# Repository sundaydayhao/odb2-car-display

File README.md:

# P4 汽车副屏

ESP32-P4 Function EV Board **v1.4**，原配 **7 寸 1024×600 触屏与 MIPI 摄像头**，ESP-IDF **5.5.x**、LVGL 9.2。
车辆仪表、影音中心（SD/在线 MP3、RDA5807M FM 电台、摄像头）、小智车辆查询与设备控制、闹钟、SD 诊断记录、Wi-Fi STA（路由器或手机热点）、HTTPS 上传与签名 OTA。
已移除微雪 S3 的屏幕/触摸实现，仅保留 **ELM327 BLE** 车辆数据入口，不恢复有线总线采集，也不创建 `projects`。

完整接线、C6 配套固件、配网、语音绑定、日志回放和本地服务器使用见 **[P4 上板与联调](docs/P4_BRINGUP.md)**。
尚无云服务器时，默认不上传、不自动升级；摄像头功能已启用，开机不自动采集，可通过页面或小智开启和拍照；麦克风开机后在本机识别唤醒词，唤醒后才向小智上传本轮语音。

当前固件 **0.4.0**：底部七页包含仪表、影音中心和地图轨迹。影音中心提供音乐、FM 电台、摄像头三个页签；语音助手和闹钟位于设置中。音乐支持 SD 卡根目录或 `music` 文件夹中的 MP3，也支持用户提供的 HTTP/HTTPS MP3 直链，音量统一在声音设置中调整。FM 默认 I²C0 / GPIO2 SDA、GPIO3 SCL，支持调谐、硬件搜台、收藏和全局音量；声音经模块模拟 L/R 输出，见 [FM 接收器](docs/FM.md)。地图轨迹提供离线中国概览、缩放拖动与独立串口 GPS 轨迹，未定位时显示中国地图。ATGM336H-5N 默认使用 GPIO4 / UART1 / 9600，见 [地图与接线说明](docs/MAP.md)。DHX30 温湿度空值显示在驾驶页面。摄像头默认编入，可预览、拍照保存和查看相册。

小智已注册 15 个设备 MCP 工具，可查询水温等真实车辆数据、调节音量、操作 FM 和音乐、设置闹钟及拍照。播放操作在语音回复结束后执行；缺失或过期的车辆值明确返回不可用。闹钟使用北京时间，支持单次、每天重复和倒计时；设备需保持通电。在线按歌名点歌仍需提供音乐服务/API，当前为直链播放及保存音源。详见 [小智接入与验证边界](docs/VOICE_CONTROL.md) 和 [影音中心](docs/MEDIA.md)。

2026-09-20：音乐列表移除手动刷新按钮，顶部增加播放状态及全局声音入口，音乐与语音共用保存音量；地图页去掉内层重复标题，行程与地图使用不同图标。板端补齐 B02-Z 会话握手、按能力位图分频读取、燃油流量/大气压力和连续采样的油耗/行程计算。用户车辆已确认为 2019 凯美瑞 2.5L 汽油版，具体可用范围和未接入项目见 [车辆参数映射](docs/VEHICLE_DATA_2019_CAMRY.md)。

界面视觉重设计：使用 Inkscape 制作可编辑的深浅主题稿、统一线条图标及本地音乐插画，落实到七页 LVGL 界面和设置。设计源文件与导出方式见 [CABIN 双主题设计](docs/design/cabin/README.md)。

0.3.15：顶部 SD 卡图标随识别状态更新，未检测到卡为灰色、可用为绿色、存储异常或记录已满为红色；运行中插卡会重新识别，拔卡后停止记录并更新状态。保留已有记录，不自动格式化或清空。

0.3.14：顶部状态栏与设置侧栏统一使用机身加圆形镜头的摄像头图标，支持状态颜色、深浅主题和选中态；界面预览检查通过。

0.3.13：修复打开摄像头本地预览时报“连接或格式异常”的格式请求参数。SC2336 实板已完成两次连续采集、关闭和重新打开测试，用户确认屏幕画面正常，详见 [上板记录](docs/P4_BRINGUP.md#8-验收顺序)。

0.3.12：针对联网后首次唤醒的编码等待，将本次语音编码器状态优先放入片内 RAM；已编译、烧录并确认实际分配位置，首句实测结果待补入。保留待机提前连接、约两秒真实唤醒录音和官方自动对话流程，回复后可以直接追问，空闲结束由服务端通知。

0.3.9 最终实板已验证唤醒及免唤醒直接追问，两轮回复各完整播放 105 帧，用户确认正常；随后恢复待唤醒。开机首次 DHCP 失败后自动恢复，在约 47 秒时联网；首次地址获取失败的原因仍未根治，不能把本次恢复成功视为长期无线稳定性验收。

保留 0.3.8 Wi-Fi 修复：关联、获取 IP 和失败分开显示；单轮最多三次连接、一次 DHCP 重新申请和一次无线接口恢复，耗尽预算后停止，用户重新选择网络可再次连接。

蓝牙为手动扫描、从列表选择连接；成功连接的设备自动保存，开机或意外断开只重连一次，失败后停止。0.3.6 已实测十五秒扫描结束后保持待选，没有自行连接或重复扫描；后续版本保持同一蓝牙实现。适配器暂不在现场，实际连接/保存/重连仍待验收。

0.3.7 对连接期间缓存的语音按六十毫秒一帧发送；该轮实板连续两次唤醒均收到服务端识别与语音回复，分别接收并播放 76、55 帧后回待机，用户确认听到回复，无重启。用户随后在路由器网络再次遇到获取 IP 卡住，0.3.8 继续针对网络恢复排障。

0.3.5：修复唤醒后的 MCP 初始化、客户端身份和连接时序，待绑定设备优先显示绑定码；扩充 Opus 编码任务栈以修复首次聆听时重启，后续实板编码/播放的最小剩余栈为 22,856 字节。
首次使用须在联网后说「你好小智」，到「设置 → 语音助手」查看绑定码，并在 [小智控制台](https://xiaozhi.me) 添加设备；仅连接热点尚未完成绑定。现场验证进展见 [P4 上板与联调](docs/P4_BRINGUP.md#8-验收顺序)。

2026-09-14：Android 采集 App 更新至 0.2.0，提供采集／记录／设置三页、浅深色主题和大屏分类设置，验证范围见 [App 说明](android-app/README.md)。
另有独立的 [OBDNode-C3 采集固件与硬件包](obd_interface/README.md)，源码、KiCad 原理图/PCB、器件库、3D 模型和烧录夹具均位于同一板级目录，包含停车低功耗策略。
主采集板 A1 已把 16 针直焊孔、蓝牙、CAN 和电源电路整合并完成布线，ERC／DRC／未连接项／原理图一致性均为 0；[完整 OBD 板级工程与验证记录](obd_interface/hardware/obd-ble-node/README.md)。现有插头适配、射频和停车电流仍待实物验证，不能直接用于量产；`mechanical-reference/` 只保留早期孔位对照件。

历史记录（网络播放已在 0.4.0 删除）：2026-09-11 / 固件 0.2.6 底部新增第六页「多媒体」，提供联网 MP3 音乐、网络电台、播放暂停、切换曲目/电台、停止与音量控制。
「设置 → 多媒体」保存自定义音乐/电台直链；开机不自动播放，广播通过网络收听，功能与音源说明见 [当前影音中心](docs/MEDIA.md)。
网络设置自动扫描附近 Wi-Fi，显示信号、加密方式和连接状态；点选热点后输入密码连接，开放热点无需密码，提供重新扫描与忘记网络。
设置采用平板双栏布局，左侧固定八个分类，右侧内容限制为 640 像素宽；打开齿轮默认进入显示与外观，会话内记住最后使用的分类。
「设置 → 显示与外观 → 界面主题」提供六张配色预览卡片，点选立即应用并自动保存。
浅色外观为清爽白、晴空蓝、暖沙米；保留夜行霓虹、熔岩赛道、酸性机能三种深色外观。仪表和设置页同步换色，未保存外观时默认清爽白，已有选择继续保留。
顶部状态图标和齿轮统一靠右，包含蓝牙图标，移除「搜索设备」等连接进度文字；全部设备设置集中到分类设置页。
「设置 → 蓝牙设置」点击「扫描设备」，再从名称/地址列表点选连接；可断开或忘记已保存设备。开关重启后保留，关闭后释放适配器供手机采集。
在「设置 → 网络与连接」从扫描列表选择手机热点，仅输入密码即可连接并保存；设备只运行 STA，连接失败也不开 AP。
新增 **[Android 采集 App](android-app/README.md)**，直接连接 BLE 型 ELM327，限时监听 CAN 或记录标准诊断事务，保存到手机并导出供离线分析。

## 语音唤醒与连续对话

连接 Wi-Fi 并完成校时后，说 **“你好小智”**，等小智回应后直接说问题，无需触摸或按住按钮。
回复结束后可以直接追问，不用再次唤醒；一段时间没有说话，服务端结束会话后才回到待唤醒。“设置 → 语音助手”显示唤醒词、状态和首次绑定码；绑定完成后重新唤醒。
待机音频只在本机处理，不上传；真实唤醒后上传约两秒唤醒音频及对话，断句与空闲结束由服务端控制。模型打包进应用，保持原分区及签名 OTA/回滚流程。
麦克风监听与音乐输出可同时工作；检测到唤醒后，音乐暂停。回复时不接受新的唤醒，避免设备声音再次触发。
各版本的实际唤醒、连续对话、响应时间和已知问题见 [P4 联调说明](docs/P4_BRINGUP.md#8-验收顺序)。

## 使用

1. 将支持 BLE 的 ELM327 适配器接到车辆诊断口，车辆上电。
2. 断开手机诊断软件与适配器的连接，多数适配器只允许一个客户端。
3. 首次进入「设置 → 蓝牙设置 → 扫描设备」，点选自己的适配器连接。每次扫描十五秒，扫描不会自行连接。
4. 成功初始化的适配器会被保存；下次开机、重新开启蓝牙或意外断开时只尝试重连它一次，失败后停止，等待手动选择。手动断开、关闭或忘记不会立即连回。
5. 顶部蓝牙图标显示连接状态，详情在「设置 → 蓝牙设置」查看；缺失车辆数据为 `--`。

P4 通过板载 C6 提供 Bluetooth LE，不支持 Classic SPP；标注“蓝牙 ELM327”的适配器不一定是 BLE。
参见 [官方 v1.4 板卡说明](https://docs.espressif.com/projects/esp-dev-kits/en/latest/esp32p4/esp32-p4-function-ev-board/user_guide_v1.4.html)。
适配器的蓝牙串口传输的是 ELM ASCII 指令/响应，本机不会把每个通知包误当成独立 CAN 帧。

## 已实现

- NimBLE Central 手动扫描、列表点选连接，最多显示十六个可连接设备；已保存设备只自动重连一次，失败不循环扫描或切换其他设备。
- 按完整地址和地址类型区分同名设备；自动发现服务、特征与真实 CCCD，支持 Notify/Indicate。
- FFF0、FFE0、Nordic UART 三类串口服务，以及自定义服务/特征 UUID。
- MTU 协商、写入应答/无应答、通知分片拼接、单指令串行事务、`>` 结束符和容量检查。
- 超时或溢出后关闭当前连接，隔离迟到响应；用连接代次防止旧连接数据进入新会话。
- ELM/STN 身份检查、AT 初始化、自动识别 ISO 15765-4 协议 6/7/8/9。
- 支持 PID 位图查询和单 ECU 固定；11 位/29 位响应头、填充字节、边界校验以及有界 ISO-TP 重组。
- 每项数值独立失效时间；断开连接立即清空实时有效标记，UI 不阻塞等待蓝牙。
- 可选 BLE 配对、明确配置的 SMP passkey、NVS 绑定保存。不自动覆盖冲突的旧绑定。
- 乐鑫 `esp_xiaozhi 0.1.2` + `esp-sr 2.4.6`，说“你好小智”唤醒，按官方 AUTO 流程由服务端断句并回复；回复后继续聆听，服务端结束后回待唤醒。已接入 AEC，声学效果待实板验证；不支持回复中语音打断。
- 影音中心提供 SD/在线 MP3 播放、RDA5807M FM 接收控制和摄像头预览/拍照/相册；小智支持设备查询和控制。FM 模块尚待接线实测，摄像头不录像、不上传画面，开机不自动采集。
- SD 原始事务记录与解析快照，有界容量、掉包标记和重启恢复；HTTPS 幂等上传。
- 本地 HTTPS 服务、固件签名发布、离线回放工具；P4 双 OTA 槽、手动驻车升级及启动自检回滚。

| 数据 | 标准 PID | 单位 |
| --- | --- | --- |
| 车速 | 01 0D | km/h |
| 发动机转速 | 01 0C | rpm |
| 发动机负载 | 01 04 | % |
| 节气门开度 | 01 11 | % |
| 冷却液温度 | 01 05 | °C |
| 油量 | 01 2F | % |
| 控制模块电压 | 01 42 | V |
| 进气温度 | 01 0F | °C |
| 机油温度 | 01 5C | °C |
| 进气歧管绝对压力 | 01 0B | kPa |

只轮询所选 ECU 声明支持的参数。增压相对压力不使用固定大气压猜测；档位、胎压、
变速箱温度、续航、油耗等尚未接入的参数保持不可用。副屏固件不执行清码、刷写、控制执行器或全总线监听。
手机 App 的 CAN 监听单独运行，只记录适配器在诊断口可见的经典 CAN；手机采集前需在副屏蓝牙设置中关闭车辆连接（旧固件可关闭副屏），避免争用适配器。

## 配置

在 `idf.py -B display_board/build menuconfig` 的 **ELM327 BLE Dashboard** 中配置：

- 设备选择在副屏蓝牙扫描列表完成，旧名称/地址过滤配置不再参与连接；随机地址未绑定且发生轮换时，需要重新扫描选择。
- UUID：三项同时设置或全部留空，详见 [BLE 协议实现](docs/ELM327_BLE.md)。
- 配对：默认按服务的加密要求触发；写入特征需加密的适配器可打开预先配对。
- 指令间隔：默认 50 ms；普通响应 1500 ms；初次车辆搜索 20000 ms。

工程使用显示板自己的配置：默认值由 `display_board/sdkconfig.defaults` 和 `display_board/main/Kconfig.projbuild` 提供，
当前构建配置保存在 `display_board/sdkconfig` 中，依赖缓存保存在 `display_board/managed_components/`，包含 BLE、屏幕和 PSRAM 参数。

## 构建与烧录

显示板构建产物位于 `display_board/build`，已经切换为 P4 目标。使用本机 IDF 5.5.5 环境包装器：

```powershell
.\tools\idf55.ps1 build
# 核对 v1.4 的 USB-to-UART 口，把 COMx 替换为实际串口
.\tools\idf55.ps1 -IdfArgs @('-p', 'COMx', 'flash', 'monitor')
# 配套 C6 无线固件，产物在 display_board/build/c6，通过 C6 独立编程口烧录
.\tools\build_c6.ps1
```

按官方要求使用 USB/稳压电源，不要直接接车辆 12 V。
使用 16 MB Flash、两个 6 MB 应用槽；主应用起始地址 `0x20000`。
首次在 P4 上使用完整 `flash` 写入新的引导程序、分区表、otadata 和应用，不能套用旧 S3 的地址或只执行 `app-flash`。
NVS 不会在失败时自动擦除；没有卡时记录状态为不可用，SD 卡不会被自动格式化。

## 代码结构

两块实体板已经按板级职责各自保存完整工程：

| 目录 | 板卡与职责 |
| --- | --- |
| `display_board/` | ESP32-P4 显示板板级包：`main/` 固件源码、`hardware/` 原理图/PCB/器件库/3D 外壳、`managed_components/` 和 `sdkconfig` |
| `obd_interface/` | ESP32-C3 OBD 接口板板级包：`main/` 固件源码、`hardware/` 原理图/PCB/器件库/3D/夹具、独立 `sdkconfig.defaults` |

显示板使用 `display_board/CMakeLists.txt`、`display_board/sdkconfig`、`display_board/managed_components` 和 `display_board/build` 作为独立 ESP-IDF 工程；仓库根目录不再保存某块板的源码或工程配置，只保留跨项目工具、文档和共享测试输出。OBD 接口板是可独立配置、构建和烧录的 ESP-IDF 工程。

| 文件 | 职责 |
| --- | --- |
| `display_board/main/elm327_ble.c` | NimBLE 连接、服务订阅、串行传输和重连 |
| `display_board/main/elm327_protocol.c` | 有界 ASCII/ISO-TP 响应解析，不依赖硬件 |
| `display_board/main/obd2.c` | AT 会话、能力发现、参数调度与快照发布 |
| `display_board/main/obd2_decode.c` | 数值换算和逐字段过期策略，不依赖硬件 |
| `display_board/main/ui.c` | 官方 BSP 屏幕/触摸、线程锁及显示模型映射 |
| `display_board/main/dashboard.c` | 七页彩色界面、主题、手动导航、显式演示模式 |
| `display_board/main/service_panel.c` | 唯一齿轮入口、分类设置、屏幕配网、外观、语音/摄像头/上传/更新交互 |
| `display_board/main/voice_service.c`、`display_board/main/camera_service.c` | 小智音频链路与本地摄像头预览 |
| `display_board/main/recorder.c`、`display_board/main/cloud_service.c` | SD 记录、HTTPS 上传、签名 OTA |
| `display_board/main/device_services.c`、`display_board/main/network_service.c`、`display_board/main/device_console.c` | NVS 设置、热点 STA 与串口配置 |
| `tools/lab_server.py`、`tools/replay_recording.py` | 本地诊断服务、升级发布与原始记录回放 |
| `android-app/` | Android BLE 连接、ELM 会话、前台限时采集、本地记录与导出 |
| `tools/analyze_android_capture.py` | 手机 JSONL 完整性检查、CAN 帧/通信事件 CSV 与汇总 |

## 验证

2026-09-15 / 0.3.0：唤醒词版本在 ESP-IDF 5.5.5 下构建通过，应用 5,731,648 字节，现有 6 MiB OTA 槽剩余 559,808 字节。
5 项 C 测试、18 项 Python 测试及 8267 个同源界面标签检查通过，语音设置页已人工查看。
固件内 WakeNet/VAD 共 579,144 字节，与固定版本组件模型逐文件核对一致；随后完整烧录到 COM28，四个镜像校验通过。
65 秒启动观察确认版本、Wi-Fi 连接及校时、BLE 扫描和唤醒待机状态，串口已释放；实板声学表现仍待验证，日志见 `build/flash-0.3.0-20260915/`。

新实现与实板待验收边界见 [P4 上板与联调](docs/P4_BRINGUP.md)。原有
[产品与系统总体规划](docs/PRODUCT_ARCHITECTURE.md) 保留为历史讨论，不能作为当前平台选择或功能已验证的依据。

本机运行 `.\tools\run_host_tests.ps1`，测试产物均在 `build` 内。
2026-09-14 提交前复核：P4 0.2.6 在 IDF 5.5.5 下构建通过；4 项 C 测试、18 项 Python 测试和 8265 个同源界面标签／交互检查通过。本轮未新增实板烧录或实车验证。

2026-09-11 / 0.2.2：P4 构建和 3907 个同源界面标签/交互检查通过，已在 COM28 完整烧录并校验。
14 项实板蓝牙检查通过：关闭后停止扫描、关闭/开启状态重启保存、禁用时拒绝重连、开启及手动重连恢复扫描；最终恢复蓝牙开启，串口已释放。
本次未连接真实适配器，设备断连和正在传输时切换仍待实机覆盖。日志在 `build/flash-0.2.2-20260911/`。

2026-09-11：P4 0.2.1 构建通过，应用约 2.50 MiB，6 MiB OTA 槽剩余 58%；2 项 C 测试、18 项 Python 测试通过，
同源 UI 检查 3570 个标签无错误。Android 0.1.0 Debug APK 构建、17 项协议测试和 Lint 检查通过。
随后按用户要求在 COM28 完整烧录 P4 0.2.1，四个镜像写入校验通过；观察 65 秒无崩溃或再次重启，屏幕/触摸初始化、STA 启动和 BLE 扫描正常。
仍有 C6 版本不匹配、SD 卡不可用提示，热点尚未配置。未烧录 C6 或连接 Android 手机；热点连接、实体触摸/亮度、真实 ELM 采集与手机后台运行仍待验收。
本次烧录与启动日志位于 `build/flash-0.2.1-20260911/`。

2026-09-08：IDF 5.5.5 下 P4 主固件和配套 C6 固件均构建通过；2 项 C 协议/升级策略测试、
10 项 HTTPS/签名/回放测试通过，同源 UI 检查 4808 个标签无错误，并人工检查截图。
启用公钥的 OTA 分支另行构建通过，默认配置已恢复为未配置服务器/信任目录、禁止台架升级绕过。
随后已在 COM28 完整烧录 P4，并修正 Hosted 传输池片内内存不足、Wi-Fi/BLE 并发初始化共享总线导致的重启。
修正后观察 65 秒无崩溃/重启，屏幕和 GT911 初始化成功、BLE 持续扫描、串口状态正常；物理触摸操作仍待人工验收。
板载 C6 报告版本不匹配，本轮未烧录 C6；存储卡初始化失败、热点未配置。
尚未验证实板音视频、真实车辆连接、设备端上传和 OTA 掉电回滚。
测试包含每个通知分片边界、回显、提示语、多个 ECU、两类响应头、ISO-TP 序号错误、截断、溢出、
负响应、不支持参数、换算、逐字段过期和随机字节输入。板端 UI 同源测试见 [UI 说明](docs/UI_DESIGN.md)。

实际适配器的 UUID、配对方式和响应行为需要实机确认，软件测试不等同于已经连通真实车辆。
**历史 S3 验证（不适用于当前 P4 固件）**：2026-09-06 曾构建并烧录到 COM9，写入校验成功；启动后观察 65 秒，
屏幕/触摸初始化及 BLE 扫描正常，未发现崩溃。观察期间未连接到匹配的适配器，尚未完成真车数据验收。

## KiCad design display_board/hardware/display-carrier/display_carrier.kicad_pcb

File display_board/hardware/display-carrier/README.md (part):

# OSPTEK P4C5 / P4C6 显示底板

2026-09-25，修订 R：五类器件、八个位置按价格/交期调整，原理图、PCB 与单板 BOM 同步。导出不含批量、备料或起订量放大；误配商品与 DNP 单独列出。见 [当前采购说明](PROCUREMENT.md) 和 [成本、交期与兼容性](COST_REDUCTION.md)。

**当前主工程：修订 R（单板 BOM 与价格/交期调整）。** 保留触摸/LCD 穿孔，调整主控和摄像头接口；打开本目录 `display_carrier.kicad_pro`。`../display-carrier-revision-L/` 保留历史 L1 副本。

2026-09-25，转角修正：消除四处 MIPI 等长补偿锐角，改用展开的 45° 补偿段；增加实际铜线转角检查，物理 DRC、差分匹配与参考地复核通过。见 [布线复核](ROUTING.md)。

2026-09-25，修订 Q：99 个电阻和 56 个电容改为 0402，原理图/PCB/采购表同步。采用嘉立创 JLC04161H-3313、名义 1.6 mm；DSI/CSI 六组差分已布线并补内层参考地、换层回流过孔和时钟分段屏蔽。工程仍为部分布线，电源/USB/射频/音频及原有电路缺口尚待继续。见 [0402 清单](PASSIVE_SHRINK.md) 与 [布线依据和检查范围](ROUTING.md)。

2026-09-24，修订 P：按立创大陆站库存完成全板定料/替换；ES8388、FSV4730、SHT40 膜版及开关、电感、电容等已同步 SCH/PCB。85 个具体料号覆盖 328 个装配位置（84 个直营、1 个合作供应）；仅 F300 需电池条件定型，主控/ML307 保留。新 FM 不支持 RDS，Codec/FM 需驱动迁移。见 [替换与库存核查](SOURCING_REVIEW.md) 和 [当前单板采购表](PROCUREMENT_PER_BOARD.csv)。

2026-09-24，修订 N：主控上移 6 mm，LCD 焊盘间距增至 8.88 mm；摄像头座移至右下方。12 根 MIPI 信号在独立临时板几何试连通，主工程仍未布线。见 [本轮布局与试布边界](MIPI_LAYOUT.md)。

2026-09-24，修订 L1：J300 改为 J301 同款 **JST B2B-PH-K-S(LF)(SN) / C131337**，PH 2.0 mm、立式 2Pin。原理图、PCB、3D 和采购表同步，电池 1 脚为正极、2 脚接地。PH 额定 2 A（AWG24），原高功率电池预算不再适用，F300 改为待选型；详见 [端子变更与电流限制](J300_TERMINAL.md)。

2026-09-23，修订 L：按 **100 块＋20% 备料**建立立创优先采购表。每板 300 个装配位置当前归入 72 个具体立创料号（L1 合并 J300 后），鱼鹰核心板/ML307 两项单采，18 个位置仍需闭合；库存为当日未锁定快照。麦克风、模拟开关、FM 稳压器和功放分压已同步 SCH/PCB/封装。见 [采购与替代依据](PROCUREMENT.md)、[现行单板表](PROCUREMENT_PER_BOARD.csv)、[逐位号表](PROCUREMENT_REFERENCES.csv)。

2026-09-23，修订 K：**F 面朝后壳，B 面朝屏幕**。FPC 座、高 2Pin 接口及全部器件本体集中到 F 面，增加触摸 10×3 mm、LCD 20×3 mm 两处实际穿线槽。B 面无器件本体，但通孔脚仍名义露出最高约 2.4 mm，需绝缘间隙；槽位与穿板线长待实物确认。见 [正反面装配说明](SCREEN_BACK_ASSEMBLY.md)。

修订 J 保留：L400 改为国产长江微电 **FEXU0640S2R2MGS / C54140025**，2.2 µH，6.2×6.0×4.0 mm；SCH/PCB/3D 已同步。见 [电感选型与核算](INDUCTOR_SELECTION.md)。

修订 I 保留：SIM 改为 **GCT SIM8066 按压自锁 Nano-SIM**，从屏幕正视的右侧推入、再次按压弹出。原理图/PCB/3D 已同步；卡检测及上拉按 ML307A 手册修正。见 [SIM 卡座与外壳要求](SIM_SOCKET.md)。

修订 H 保留：新增板载 **RDA5807M**，音频改为 **ES8389 + 两颗直接焊载板的 MEMS 麦克风 + 两只 NS4150B / 两路扬声器接口**，参考 ESP32-S31-Korvo-1 官方结构；主控仍为 P4C5/P4C6。见 [音频架构与固件迁移](AUDIO_ARCHITECTURE.md)。

修订 G 的原始测量继续保留：总成顶部到原平面折后尖端 **触摸 7.5 mm / LCD 46.1 mm**。板框 145×85 mm，PCB 顶部偏移 2.50 mm。修订 K 将坐标改为屏幕背视，插座暂加 4 mm 穿板长度补偿，不能当作已确认的插接位置；光照/温湿度及隔热槽保留。见 [当前布局](FPC_FIT_REVIEW.md)、[传感器](CABIN_SENSORS.md)。

当前 20 页原理图、361 个电路封装＋4 安装孔，338 个实体器件均有可加载模型，默认装配 331 个；7 个互斥配置/射频调谐件保持 DNP。**部分布线，519 项未连接，整机电路尚有既有缺口，不能投板。** ERC 0 error / 13 个既有 warning；原生物理 DRC、SCH/PCB 一致性 0 违规。检查边界见 [设计状态](DESIGN_STATUS.md)。

按本轮要求放弃原裸 P4＋C6 单板方案，重新设计一块集成外围功能的底板。一个 25 × 25 mm、88 针邮票孔位置，择一贴装 OSPTEK ESP32-P4C5-Core 或 ESP32-P4C6-Core。兼容指同一 PCB 的两种装配配置，不是两个核心板同时装，也不是可热插拔的插座。

旧 `../display-singleboard/` 仅作历史记录，不作为新板的布局、电源或布线起点。本轮新增 [KiCad 工程](display_carrier.kicad_pro)、[原理图](display_carrier.kicad_sch)、[PCB 初摆](display_carrier.kicad_pcb)、[电气核算](ELECTRICAL_REVIEW.md) 和 [装配配置](ASSEMBLY_VARIANTS.csv)。已有资料包括[88 针核对表](CORE_PIN_COMPATIBILITY.csv)、[GPIO 分配](GPIO_PLAN.csv)、[可选 4G/GNSS 设计](OPTIONAL_LTE_GNSS.md)、[ML307A-GCLN 接线规划](MODEM_PIN_PLAN.csv)、[布局示意](FLOORPLAN.svg) 和 [资料版本记录](SOURCE_AUDIT.json)。

修订 C 的主要决定：蜂窝模组改为 17.7 × 15.8 mm、94 脚 LGA 的 ML307A-GCLN；采用内部 USB RNDIS 网卡作为联网首选、UART0 独立控制；3.8 V 降压和至少 2 × 220 µF 储能靠近模组布置。GPIO24/25 改为 USB 检测电源和 GNSS 有源天线电源控制，不再保留这两脚的 USB-FS 维修用途。外部 CH343P USB-C 充电/串口下载、屏幕/触摸、摄像头、SD、音频/FM 和双核心板兼容规划继续保留。

## 1. 核心板兼容性

已对照本机两款核心板的 88 针表、内部连接图、尺寸图，以及底板使用指南 2026.09.10 中的 V1.5 原理图。

| 项目 | 核对结果 / 设计决定 |
| --- | --- |
| 封装 | 两份图均为 25 × 25 mm、每边 22 针、1.0 mm 节距；C6 图片外形公差标 ±0.3 mm，按较大公差留装配余量。已导入两份 PcbLib 核对 88 脚名义坐标；共用焊盘按 C5 非 EP 版调整，详见 FOOTPRINT_SOURCES.md。公差、钢网和实际焊接仍待验证 |
| 电源 | 核心板 85/86 脚输入 3.3 V；84 脚 RTC_VBAT 接受控 3.3 V，不能悬空或直接接满电 4.2 V 电池；66 脚是 LDO 输出，不能当电源输入 |
| 共用外围 | P4 GPIO、DSI、CSI、USB 专用信号在两款 88 针表中对应一致；全部产品外设只接 P4 |
| 差异脚 | 6～11 脚分别为 C5 GPIO28/27/26/25/24/23 与 C6 GPIO15/14/13/9/8/7，不接通用外设 |
| 无线下载 | 共用 UART：4=RF_RX、5=RF_TX；RF_BOOT 用互斥 0 Ω 电阻选择 C5 的 6 脚或 C6 的 9 脚。C5 下载还需 7 脚 GPIO27 高；C6 下载需 10 脚 GPIO8 高，先核对模组已有上拉再决定底板配置 |
| 内部占用 | P4 GPIO14～19 为内部无线 SDIO，GPIO6 接无线 GPIO2，GPIO54 控制无线 EN；都不能再分给底板功能 |
| P4 启动 | 外加 CHIP_PU 复位 RC；GPIO35 接 BOOT，GPIO36 保持下载要求的高电平。GPIO34～38 不挂会影响启动采样的负载 |
| 无线天线 | 复用核心板 IPEX-1，采用厂商双频 FPC 天线，布置于后壳塑料区、避开屏幕金属背板和电池；C6 仅用其 2.4 GHz 频段。核心板 RF 焊盘不再接一条并联天线支路 |
| 软件 | 仓库 C5 产品描述为 P4 v3.x、C6 为 v1.3；采购批次需读芯片版本。P4 v1.x/v3.x 必须分别编译固件，C5/C6 的 ESP-Hosted 从机固件也分别管理。IDF 5.5 系列至少采用支持实际芯片的补丁版，v3.x 最低 5.5.3；若使用 v3.2 外部 32 kHz 晶体则按官方告知要求 5.5.5+ |

P4C6 可作成本配置，P4C5 可作双频 Wi-Fi 配置；不按目录名称推定今后批次的 P4 硅版本。

无线维修下载时需要使 P4 保持复位、GPIO54 不驱动无线 EN，再由夹具控制 RF_EN/BOOT/UART，防止并联输出争用。底板只留内部维修点；日常 P4 下载使用外部 USB-C。

OBD 通信按自研 BLE 节点规划。C5/C6 的蓝牙能力是 Bluetooth LE，不能把经典蓝牙 SPP 型 ELM327 视作可直接连接的设备；若仍要兼容该类 ELM327，需要额外的经典蓝牙桥接硬件。本版先不增加桥接器，避免扩大成本和无线调试范围。[C5 官方能力](https://www.espressif.com/en/products/socs/esp32-c5)、[C6 官方能力](https://www.espressif.com/en/products/socs/esp32-c6)。

## 2. 功能和器件选择

以下是候选器件和接口方向，尚不是已核价或已锁库存的量产 BOM。优先沿用供应商公开且可购买的型号；不要以淘宝存在同名商品代替正品、版本和持续供货确认。

| 功能 | 首版规划 | 选型与限制 |
| --- | --- | --- |
| 核心 | OSPTEK P4C5-Core / P4C6-Core | 同一封装、两套配置电阻/BOM；官方淘宝店为鱼鹰光电工厂店 |
| LCD | LCM-070WS209-A0，7 寸 1024 × 600，JD9165BA | 专用 30P、0.5 mm FPC；按用户 PDF 针序重新绘制，不能复制 OSPTEK YDP400BT001-V4 的 30P 屏口 |
| 触摸 | 独立可选的 I2C 触摸接口 | 与 LCD 座同在朝屏面，横向放置、入口同朝下；按照片镜像估算 PCB X=36 mm，横向仍待实测。预留 3.3 V、GND、SDA、SCL、INT、RST；脚序和接触面待定。当前接口器件均装配；无触摸款不接触摸排线，固件正常进入显示模式 |
| 可选 4G＋定位 | 中移 **ML307A-GCLN**，型号已由用户选定 | 17.7 × 15.8 × 2.4 mm、LGA94；同板选装 GPS/北斗、Nano-SIM、LTE/GNSS 双天线、电源及电平转换。标准 AT 固件＋内部 USB RNDIS 优先；具体固件/描述符/GNSS 并发仍需样品验证，不能用 ML307R 或 A-D 系列代替 |
| 摄像头 | OSPTEK ESP32-P4-Camera / SC2336，2 MP | 一个 24P、0.5 mm CSI 接口；按其原生 24P 定义，预留 2.8/1.8 V、电平转换及 24 MHz 时钟；公开 24P 针序没有外接 1.5 V 脚，不向 NC 引脚供电，DVDD 来源待厂家确认。J1220 和 CSI 针序已绘制；摄像头电源、时钟和电平转换仍待完成 |
| 音频 Codec | ES8388，已绘制 | 双 ADC / 双 DAC；7 位 I²C 0x10；标准 I²S，需迁移驱动 |
| 板载双麦克风 | LinkMems **LMA3729T381-OAS02 ×2** | 直接焊在 F 面，131 mm 中心距；顶声孔朝后壳，取消外接咪头小板 |
| 双扬声器 | 两个独立 4 Ω 扬声器，额定 ≥3 W 为候选要求 | 分别接 J820/J821 PH 2P，BTL 两端均不能接地；声腔/外形和采购型号待确认 |
| 双功放 | **NS4150B ×2**，已绘制 | 独立 4.68 V 降压供电，共用 AMP_EN；目标及音量限制按 THD/温升实测，不沿用旧 5 W 输出目标 |
| FM | **板载 FSV4730-D60-GU**，已绘制；无 RDS | 3.0 V 可关断电源、32.768 kHz 晶体、I²C 隔离和 J810 天线口；左右声道独立；射频与起振待验证 |
| 音源切换 | SN74LVC1G3157 ×4 | 分别切换左右声道正负两条模拟线；默认 DAC，切 FM 前先静音两只功放 |
| USB-UART | **CH343P**＋自动下载电路 | 唯一外部 USB-C 同时充电、日志、P4 烧录；D+/D−只进入 UART 桥。无线芯片另外留内部维修烧录触点，避免为日常用户增加选择拨码 |
| Nano-SIM | **GCT SIM8066-6-1-14-01-A** | 按压自锁、右侧插入、带常闭检测；当前厂家 Rev B 与实物壳体配合待核对，见 SIM_SOCKET.md |
| microSD | 带检测脚的自弹 TF 卡座，4 bit SDMMC | R0 已画 3.3 V 可关断供电和串阻；卡座 ESD 与断电 IO 防反灌尚未闭合。首版按 3.3 V 模式验证，不默认支持 1.8 V UHS |
| 电池充电 | **BQ25896**，替换原 SGM41513 候选 | NVDC、NTC、PSEL，不占用 USB 数据线；厂商给出最高 9 A 电池放电通路，按整机热设计降额。充电仍设 1～1.5 A；这里不是 9 A 充电。与旧候选不是焊盘直接替换 |
| USB 电流识别 | **TUSB320LAI**，固定 Sink | R0 用 GPIO 模式，仅使用“至少 1.5 A”信号，3 A 也保守按 1.5 A 档处理。TPS2553 限流最坏上限约 439 / 1253 mA；另计 USB 桥消耗。详见 ELECTRICAL_REVIEW.md |
| 主电源 | **TPS61088**→5 V；**TLV62569**→3.3 V | 5 V 主路改按 4 A 峰值目标及封闭壳热预算设计，3.3 V 主路目标 2 A；整机同时负载受功率预算约束。开关电流额定值不等于可持续输出电流 |
| 可选 4G 电源 | **TLV62585**：5 V→3.8 V，3 A 支路候选 | 放在右侧模组附近，按 GCLN 较新兼容手册的 **3.4～4.3 V** 约束，2 A 发射瞬态；至少 2 × 220 µF 近端储能，独立关断/主动放电/电流测点。USB 检测 5 V 和 GNSS 天线偏置单独可控，不直连 SYS |
| LCD 偏置 | **TPS65150** 候选，另加 1.8 V LDO | 可调 AVDD/VGH/VGL 和 VCOM 缓冲、可设置启动延时；需针对屏幕实际电流和断电放电顺序验算后选定，不沿用旧板齐纳钳位做法 |
| 背光 | **SY7200** 恒流升压候选 | 3 串 9 并，180 mA 总电流，LED 8.1～9.9 V；PWM 调光、开路保护、关机断电；电感/采样电阻额定值按计算选择 |
| 车内光照 / 温湿度 | OPT3001DNPR + SHT40-AD1B-R2，已绘制并放置 | 系统 I²C 0x45 / 0x44；光窗、独立通风与校准待验证，不替代板温/电池 NTC |
| 电量与温度 | 电量计接口/候选 CW2015＋板温 NTC | 电量计需对应电池模型，型号及供货再锁；板温与电池温度分别测量，不能用单个电压值宣称准确电量 |
| 按键 | RST、BOOT 侧按；电源侧滑 | 通过壳体侧孔/导向柱可操作；电源外部拨帽建议 10～14 mm，行程按实物开关定义，开关只承载控制电流 |

已将 99 个电阻、56 个电容改为 **0402（公制 1005）**，逐位号见 PASSIVE_SHRINK.md。大容量 MLCC 按直流偏压后的有效电容选 0805/1206；背光、电源电感按饱和电流选屏蔽功率封装，不用 0603 信号电感替代。功率与有效容量受限的位置保留较大封装。

## 3. 屏幕适配必须先闭合的事项

LCM PDF 给出 VDD/VDDIO 1.8 V、AVDD 9.8 V、VGH 18～20 V、VGL −8.5～−7.5 V、VCOM 典型 3.3 V。RESET、STBYB、方向脚均在 1.8 V 域，不能直拉 3.3 V。VCOM 用缓冲驱动并留校准值，不把无源分压视作已经验证的面板驱动。

STBYB、RESET、逻辑电源、偏置使能、背光各有独立控制及安全默认状态。按 PDF 第 8～9 页实施启动/关机，包括偏置电源之间的延时和掉电约 100 ms 的保持窗口；硬件电源开关转为关机请求，保留受控关机时间，不能直接在面板工作时切掉所有电源。

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
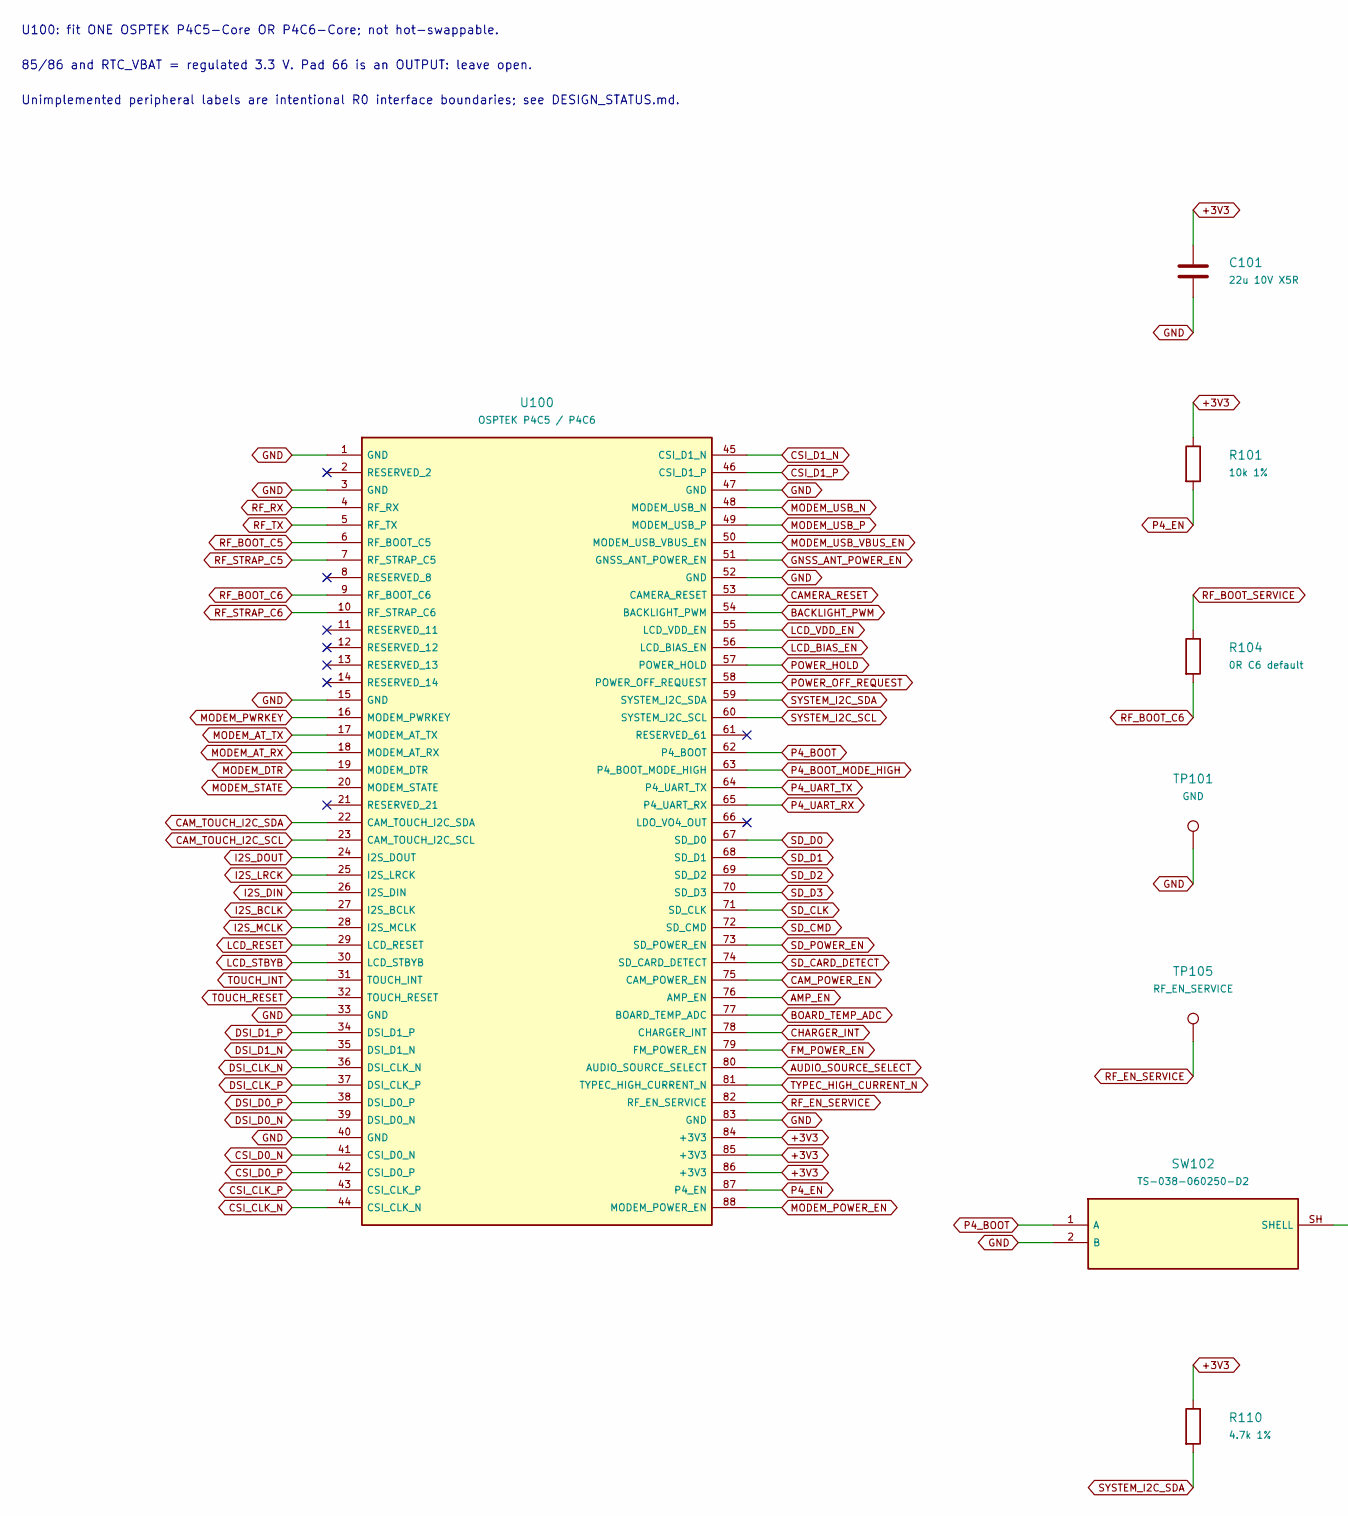
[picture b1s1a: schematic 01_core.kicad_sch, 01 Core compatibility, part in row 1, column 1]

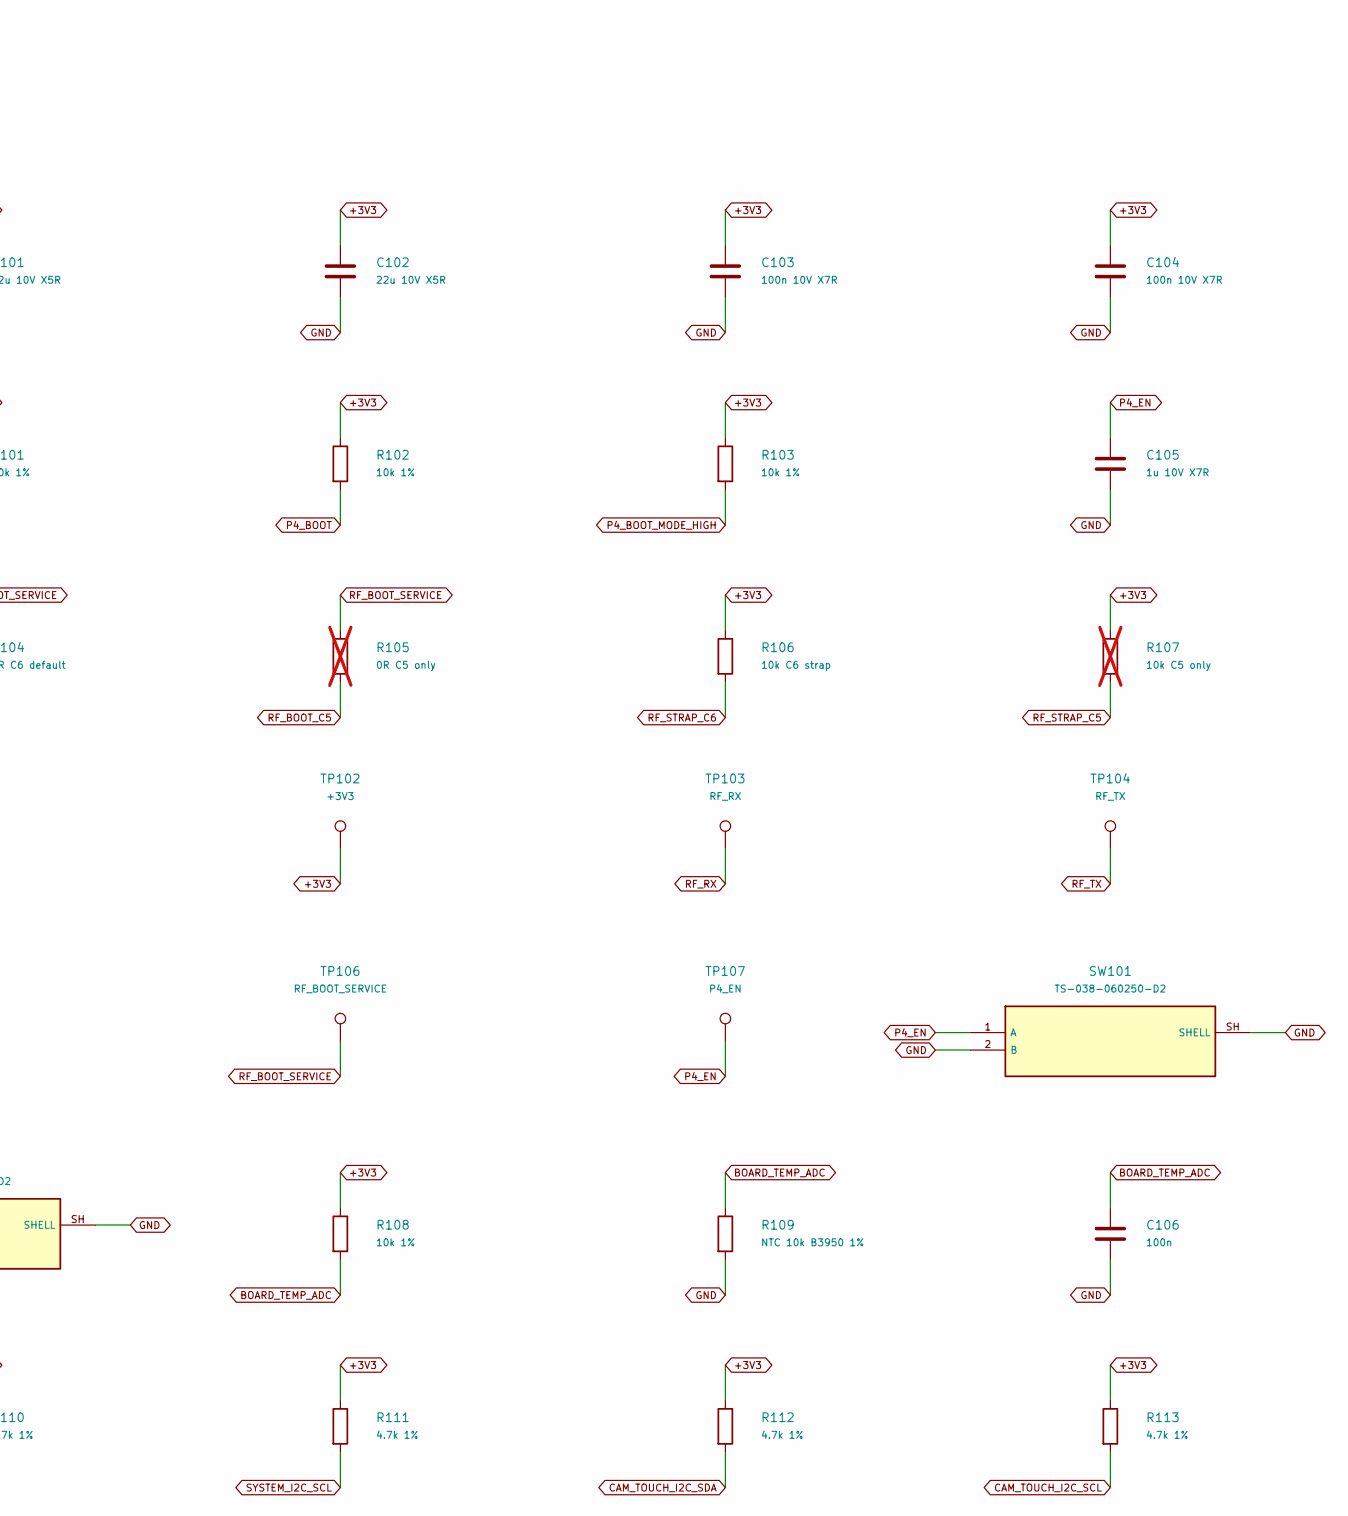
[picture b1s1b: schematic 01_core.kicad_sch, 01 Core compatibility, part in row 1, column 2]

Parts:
C101, C102: 22u 10V X5R; C_0805_2012Metric
C103, C104: 100n 10V X7R; C_0402_1005Metric
C105: 1u 10V X7R; C_0603_1608Metric
C106: 100n; C_0402_1005Metric
R101, R102, R103, R108: 10k 1%; R_0402_1005Metric
R104: 0R C6 default; R_0603_1608Metric
R105: 0R C5 only; R_0603_1608Metric; not fitted
R106: 10k C6 strap; R_0402_1005Metric
R107: 10k C5 only; R_0402_1005Metric; not fitted
R109: NTC 10k B3950 1%; R_0603_1608Metric
R110, R111, R112, R113: 4.7k 1%; R_0402_1005Metric
SW101, SW102: TS-038-060250-D2; TS038_SideKey
TP101: GND; TestPoint_Pad_D1.5mm
TP102: +3V3; TestPoint_Pad_D1.5mm
TP103: RF_RX; TestPoint_Pad_D1.5mm
TP104: RF_TX; TestPoint_Pad_D1.5mm
TP105: RF_EN_SERVICE; TestPoint_Pad_D1.5mm
TP106: RF_BOOT_SERVICE; TestPoint_Pad_D1.5mm
TP107: P4_EN; TestPoint_Pad_D1.5mm
U100: OSPTEK P4C5 / P4C6; OSPTEK_P4C5_P4C6_Compatible

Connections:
+3V3: C101.1, C102.1, C103.1, C104.1, R101.1, R102.1, R103.1, R106.1, R107.1, R108.1, R110.1, R111.1, R112.1, R113.1, TP102.1, U100.84 (+3V3), U100.85 (+3V3), U100.86 (+3V3); also elsewhere on the board
AMP_EN: U100.76 (AMP_EN); also elsewhere on the board
AUDIO_SOURCE_SELECT: U100.80 (AUDIO_SOURCE_SELECT); also elsewhere on the board
BACKLIGHT_PWM: U100.54 (BACKLIGHT_PWM)
BOARD_TEMP_ADC: C106.1, R108.2, R109.1, U100.77 (BOARD_TEMP_ADC)
CAMERA_RESET: U100.53 (CAMERA_RESET)
CAM_POWER_EN: U100.75 (CAM_POWER_EN)
CAM_TOUCH_I2C_SCL: R113.2, U100.23 (CAM_TOUCH_I2C_SCL); also elsewhere on the board
CAM_TOUCH_I2C_SDA: R112.2, U100.22 (CAM_TOUCH_I2C_SDA); also elsewhere on the board
CHARGER_INT: U100.78 (CHARGER_INT); also elsewhere on the board
CSI_CLK_N: U100.44 (CSI_CLK_N); also elsewhere on the board
CSI_CLK_P: U100.43 (CSI_CLK_P); also elsewhere on the board
CSI_D0_N: U100.41 (CSI_D0_N); also elsewhere on the board
CSI_D0_P: U100.42 (CSI_D0_P); also elsewhere on the board
CSI_D1_N: U100.45 (CSI_D1_N); also elsewhere on the board
CSI_D1_P: U100.46 (CSI_D1_P); also elsewhere on the board
DSI_CLK_N: U100.36 (DSI_CLK_N); also elsewhere on the board
DSI_CLK_P: U100.37 (DSI_CLK_P); also elsewhere on the board
DSI_D0_N: U100.39 (DSI_D0_N); also elsewhere on the board
DSI_D0_P: U100.38 (DSI_D0_P); also elsewhere on the board
DSI_D1_N: U100.35 (DSI_D1_N); also elsewhere on the board
DSI_D1_P: U100.34 (DSI_D1_P); also elsewhere on the board
FM_POWER_EN: U100.79 (FM_POWER_EN); also elsewhere on the board
GND: C101.2, C102.2, C103.2, C104.2, C105.2, C106.2, R109.2, SW101.2 (B), SW101.SH (SHELL), SW102.2 (B), SW102.SH (SHELL), TP101.1, U100.1 (GND), U100.3 (GND), U100.15 (GND), U100.33 (GND), U100.40 (GND), U100.47 (GND), U100.52 (GND), U100.83 (GND); also elsewhere on the board
GNSS_ANT_POWER_EN: U100.51 (GNSS_ANT_POWER_EN); also elsewhere on the board
I2S_BCLK: U100.27 (I2S_BCLK); also elsewhere on the board
I2S_DIN: U100.26 (I2S_DIN); also elsewhere on the board
I2S_DOUT: U100.24 (I2S_DOUT); also elsewhere on the board
I2S_LRCK: U100.25 (I2S_LRCK); also elsewhere on the board
I2S_MCLK: U100.28 (I2S_MCLK); also elsewhere on the board
LCD_BIAS_EN: U100.56 (LCD_BIAS_EN)
LCD_RESET: U100.29 (LCD_RESET); also elsewhere on the board
LCD_STBYB: U100.30 (LCD_STBYB); also elsewhere on the board
LCD_VDD_EN: U100.55 (LCD_VDD_EN); also elsewhere on the board
MODEM_AT_RX: U100.18 (MODEM_AT_RX); also elsewhere on the board
MODEM_AT_TX: U100.17 (MODEM_AT_TX); also elsewhere on the board
MODEM_DTR: U100.19 (MODEM_DTR); also elsewhere on the board
MODEM_POWER_EN: U100.88 (MODEM_POWER_EN); also elsewhere on the board
MODEM_PWRKEY: U100.16 (MODEM_PWRKEY); also elsewhere on the board
MODEM_STATE: U100.20 (MODEM_STATE); also elsewhere on the board
MODEM_USB_N: U100.48 (MODEM_USB_N); also elsewhere on the board
MODEM_USB_P: U100.49 (MODEM_USB_P); also elsewhere on the board
MODEM_USB_VBUS_EN: U100.50 (MODEM_USB_VBUS_EN); also elsewhere on the board
P4_BOOT: R102.2, SW102.1 (A), U100.62 (P4_BOOT); also elsewhere on the board
P4_BOOT_MODE_HIGH: R103.2, U100.63 (P4_BOOT_MODE_HIGH)
P4_EN: C105.1, R101.2, SW101.1 (A), TP107.1, U100.87 (P4_EN); also elsewhere on the board
P4_UART_RX: U100.65 (P4_UART_RX); also elsewhere on the board
P4_UART_TX: U100.64 (P4_UART_TX); also elsewhere on the board
POWER_HOLD: U100.57 (POWER_HOLD); also elsewhere on the board
POWER_OFF_REQUEST: U100.58 (POWER_OFF_REQUEST); also elsewhere on the board
RF_BOOT_C5: R105.2, U100.6 (RF_BOOT_C5)
RF_BOOT_C6: R104.2, U100.9 (RF_BOOT_C6)
RF_BOOT_SERVICE: R104.1, R105.1, TP106.1
RF_EN_SERVICE: TP105.1, U100.82 (RF_EN_SERVICE)
RF_RX: TP103.1, U100.4 (RF_RX)
RF_STRAP_C5: R107.2, U100.7 (RF_STRAP_C5)
RF_STRAP_C6: R106.2, U100.10 (RF_STRAP_C6)
RF_TX: TP104.1, U100.5 (RF_TX)
SD_CARD_DETECT: U100.74 (SD_CARD_DETECT); also elsewhere on the board
SD_CLK: U100.71 (SD_CLK); also elsewhere on the board
SD_CMD: U100.72 (SD_CMD); also elsewhere on the board
SD_D0: U100.67 (SD_D0); also elsewhere on the board
SD_D1: U100.68 (SD_D1); also elsewhere on the board
SD_D2: U100.69 (SD_D2); also elsewhere on the board
SD_D3: U100.70 (SD_D3); also elsewhere on the board
SD_POWER_EN: U100.73 (SD_POWER_EN); also elsewhere on the board
SYSTEM_I2C_SCL: R111.2, U100.60 (SYSTEM_I2C_SCL); also elsewhere on the board
SYSTEM_I2C_SDA: R110.2, U100.59 (SYSTEM_I2C_SDA); also elsewhere on the board
TOUCH_INT: U100.31 (TOUCH_INT); also elsewhere on the board
TOUCH_RESET: U100.32 (TOUCH_RESET); also elsewhere on the board
TYPEC_HIGH_CURRENT_N: U100.81 (TYPEC_HIGH_CURRENT_N); also elsewhere on the board

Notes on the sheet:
U100: fit ONE OSPTEK P4C5-Core OR P4C6-Core; not hot-swappable.
85/86 and RTC_VBAT = regulated 3.3 V. Pad 66 is an OUTPUT: leave open.
Unimplemented peripheral labels are intentional R0 interface boundaries; see DESIGN_STATUS.md.

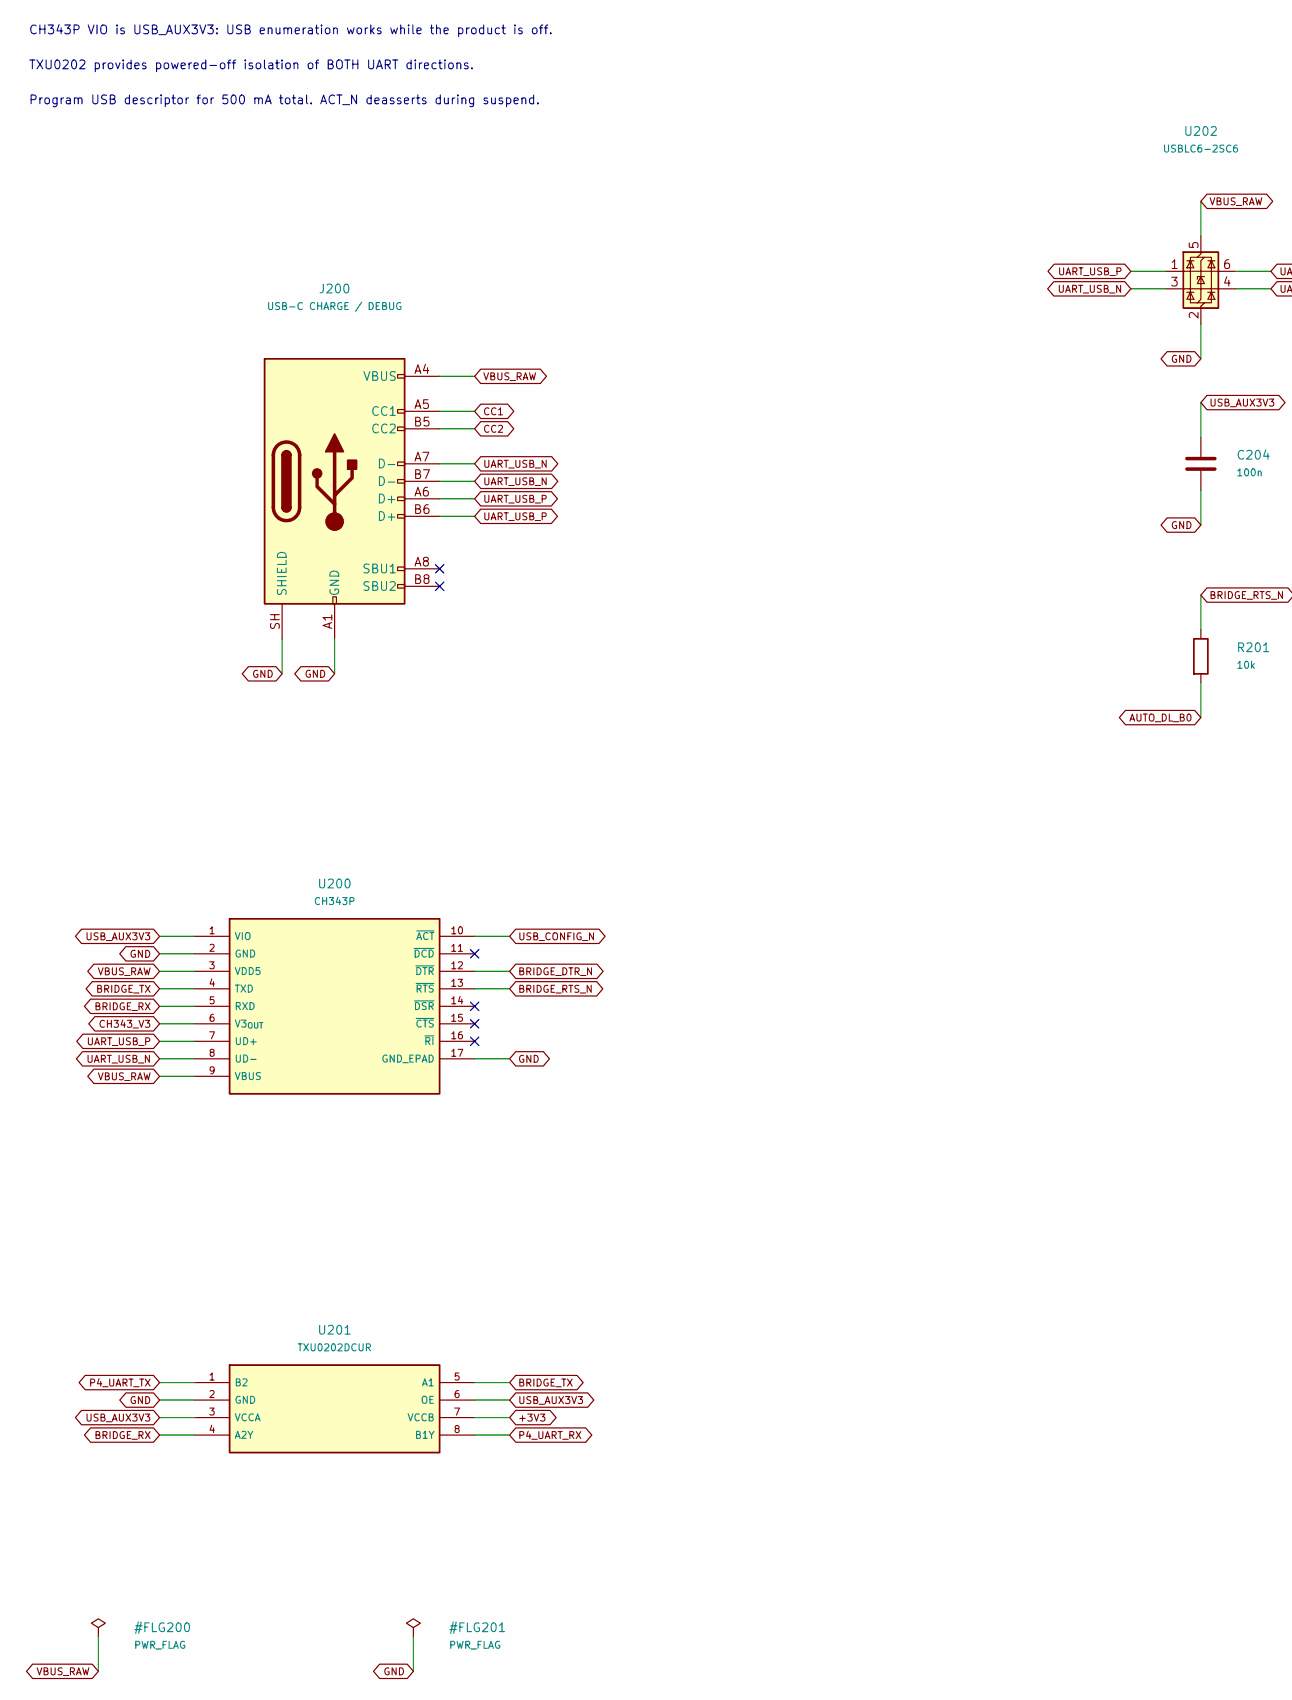
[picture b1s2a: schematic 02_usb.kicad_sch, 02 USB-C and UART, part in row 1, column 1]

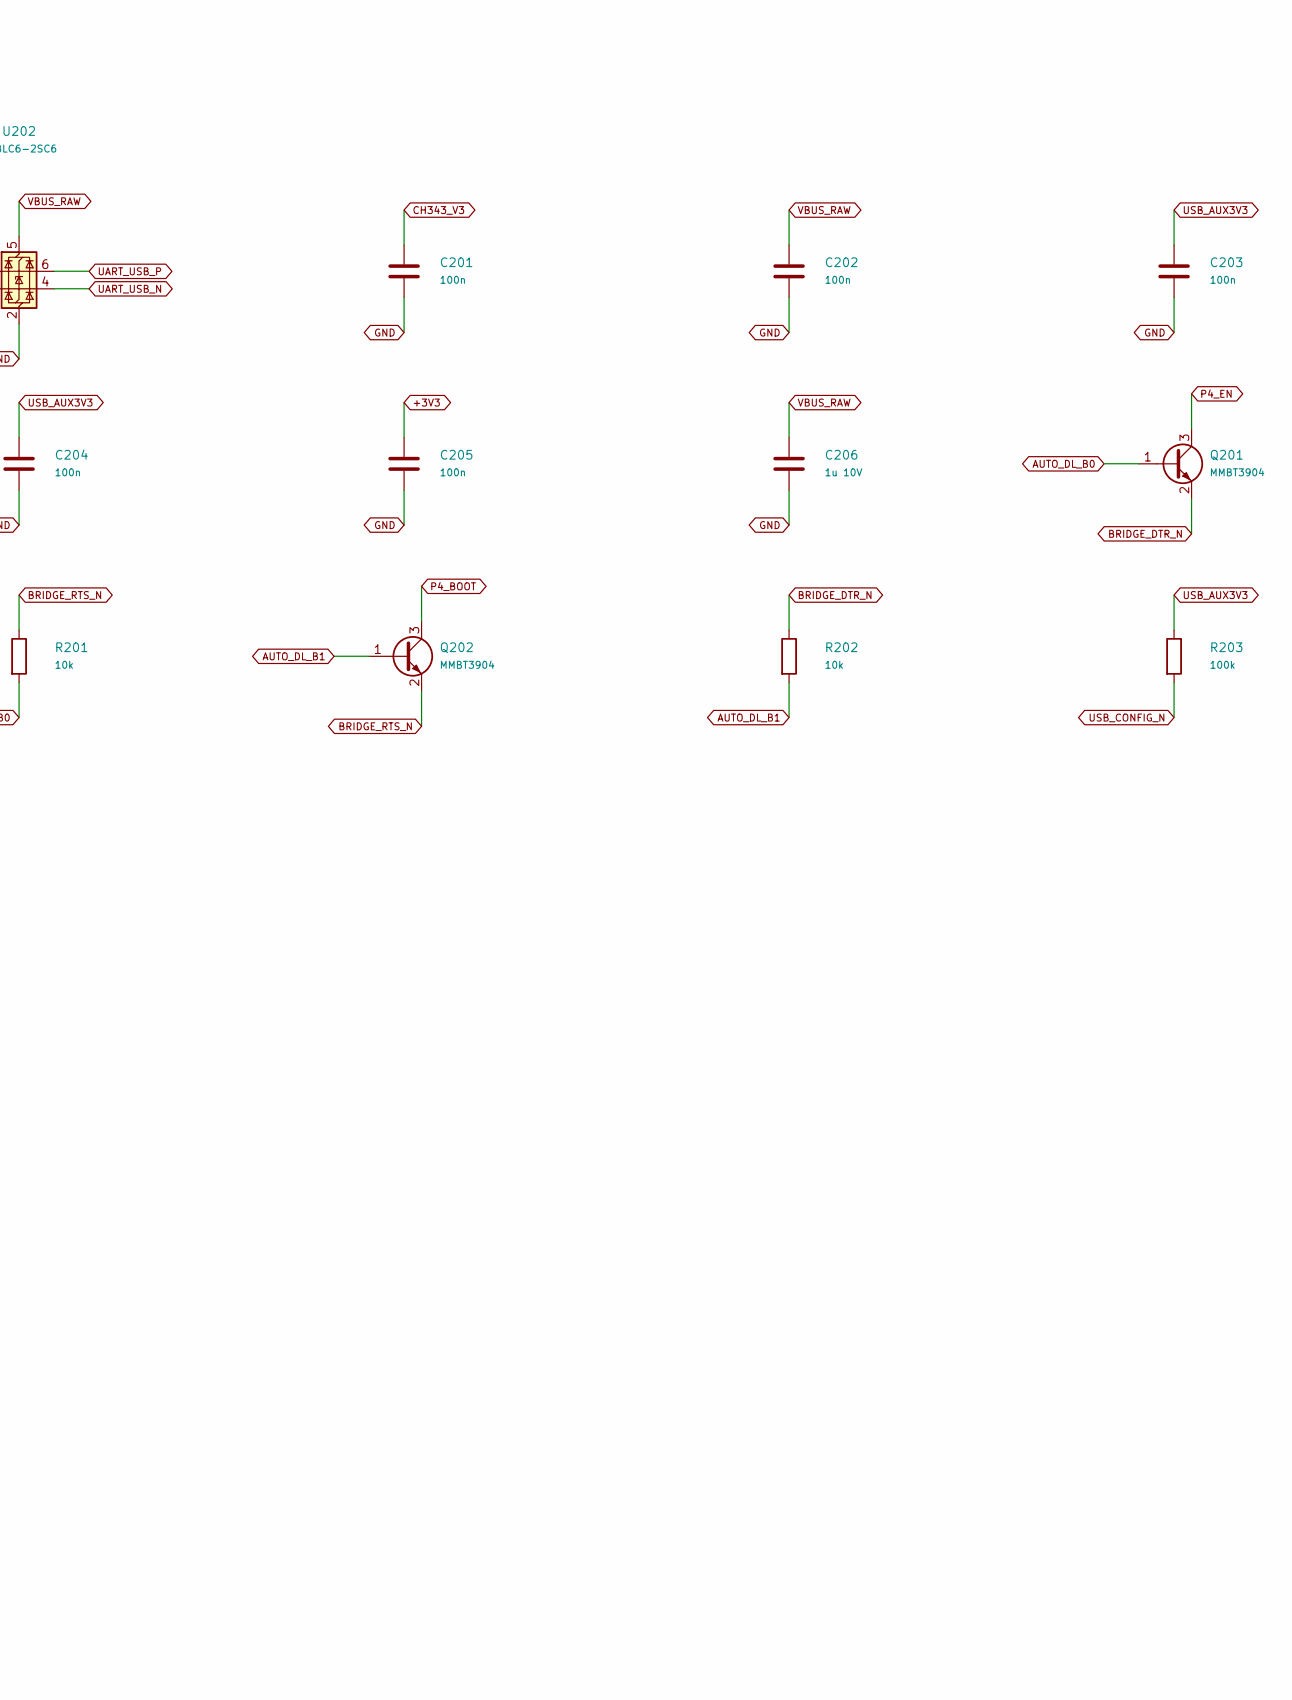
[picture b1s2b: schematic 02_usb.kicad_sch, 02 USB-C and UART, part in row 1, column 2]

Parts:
C201, C202, C203, C204, C205: 100n; C_0402_1005Metric
C206: 1u 10V; C_0603_1608Metric
J200: USB-C CHARGE / DEBUG; USB_C_HRO_TYPE_C_31_M_12_Edge
Q201, Q202: MMBT3904; SOT-23
R201, R202: 10k; R_0402_1005Metric
R203: 100k; R_0402_1005Metric
U200: CH343P; WCH_QFN-16-1EP_3x3mm_P0.5mm_EP1.8x1.8mm
U201: TXU0202DCUR; VSSOP-8_2.3x2mm_P0.5mm
U202: USBLC6-2SC6; SOT-23-6

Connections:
+3V3: C205.1, U201.7 (VCCB); also elsewhere on the board
AUTO_DL_B0: Q201.1 (B), R201.2
AUTO_DL_B1: Q202.1 (B), R202.2
BRIDGE_DTR_N: Q201.2 (E), R202.1, U200.12 (~DTR)
BRIDGE_RTS_N: Q202.2 (E), R201.1, U200.13 (~RTS)
BRIDGE_RX: U200.5 (RXD), U201.4 (A2Y)
BRIDGE_TX: U200.4 (TXD), U201.5 (A1)
CC1: J200.A5 (CC1); also elsewhere on the board
CC2: J200.B5 (CC2); also elsewhere on the board
CH343_V3: C201.1, U200.6 (V3_{OUT})
GND: C201.2, C202.2, C203.2, C204.2, C205.2, C206.2, J200.A1 (GND), J200.A12 (GND), J200.B1 (GND), J200.B12 (GND), J200.SH (SHIELD), U200.2 (GND), U200.17 (GND_EPAD), U201.2 (GND), U202.2 (GND); also elsewhere on the board
P4_BOOT: Q202.3 (C); also elsewhere on the board
P4_EN: Q201.3 (C); also elsewhere on the board
P4_UART_RX: U201.8 (B1Y); also elsewhere on the board
P4_UART_TX: U201.1 (B2); also elsewhere on the board
UART_USB_N: J200.A7 (D-), J200.B7 (D-), U200.8 (UD-), U202.3 (I/O2), U202.4 (I/O2)
UART_USB_P: J200.A6 (D+), J200.B6 (D+), U200.7 (UD+), U202.1 (I/O1), U202.6 (I/O1)
USB_AUX3V3: C203.1, C204.1, R203.1, U200.1 (VIO), U201.3 (VCCA), U201.6 (OE); also elsewhere on the board
USB_CONFIG_N: R203.2, U200.10 (~ACT); also elsewhere on the board
VBUS_RAW: C202.1, C206.1, J200.A4 (VBUS), J200.A9 (VBUS), J200.B4 (VBUS), J200.B9 (VBUS), U200.3 (VDD5), U200.9 (VBUS), U202.5 (VBUS); also elsewhere on the board

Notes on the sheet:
CH343P VIO is USB_AUX3V3: USB enumeration works while the product is off.
TXU0202 provides powered-off isolation of BOTH UART directions.
Program USB descriptor for 500 mA total. ACT_N deasserts during suspend.
